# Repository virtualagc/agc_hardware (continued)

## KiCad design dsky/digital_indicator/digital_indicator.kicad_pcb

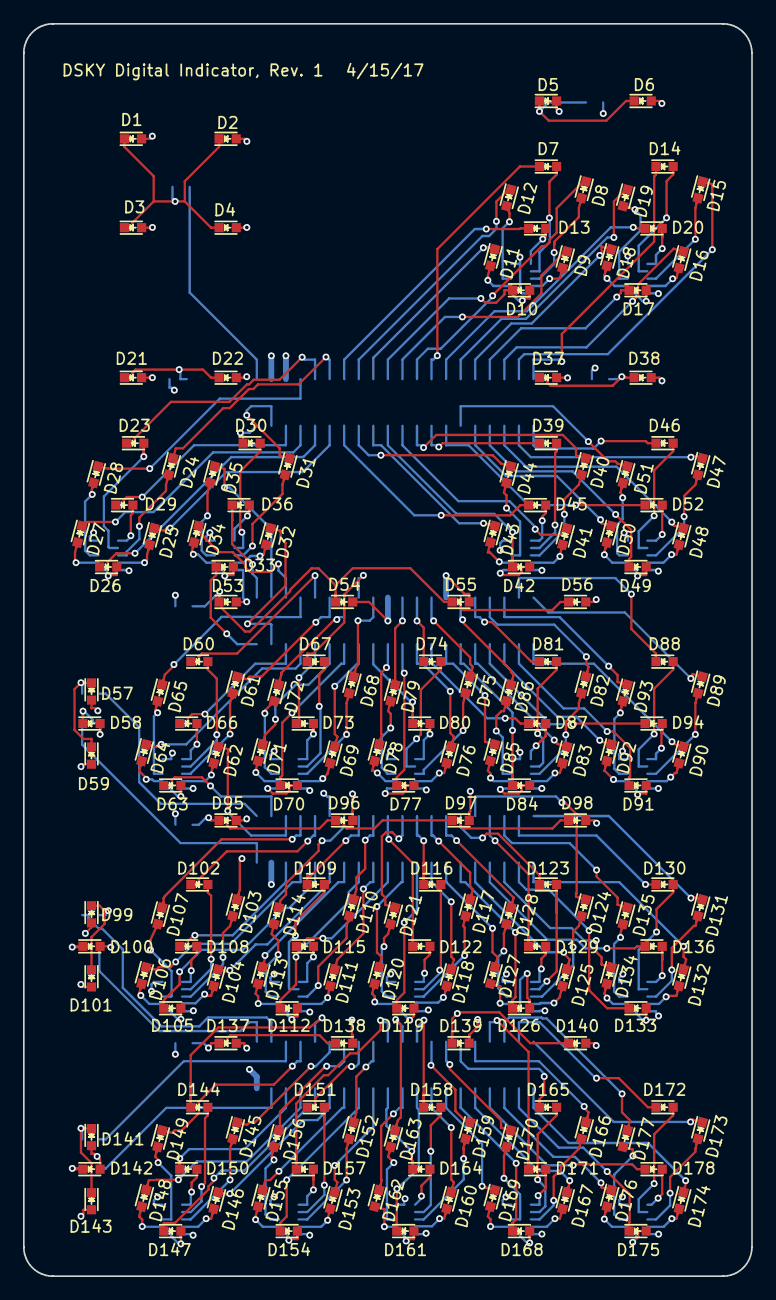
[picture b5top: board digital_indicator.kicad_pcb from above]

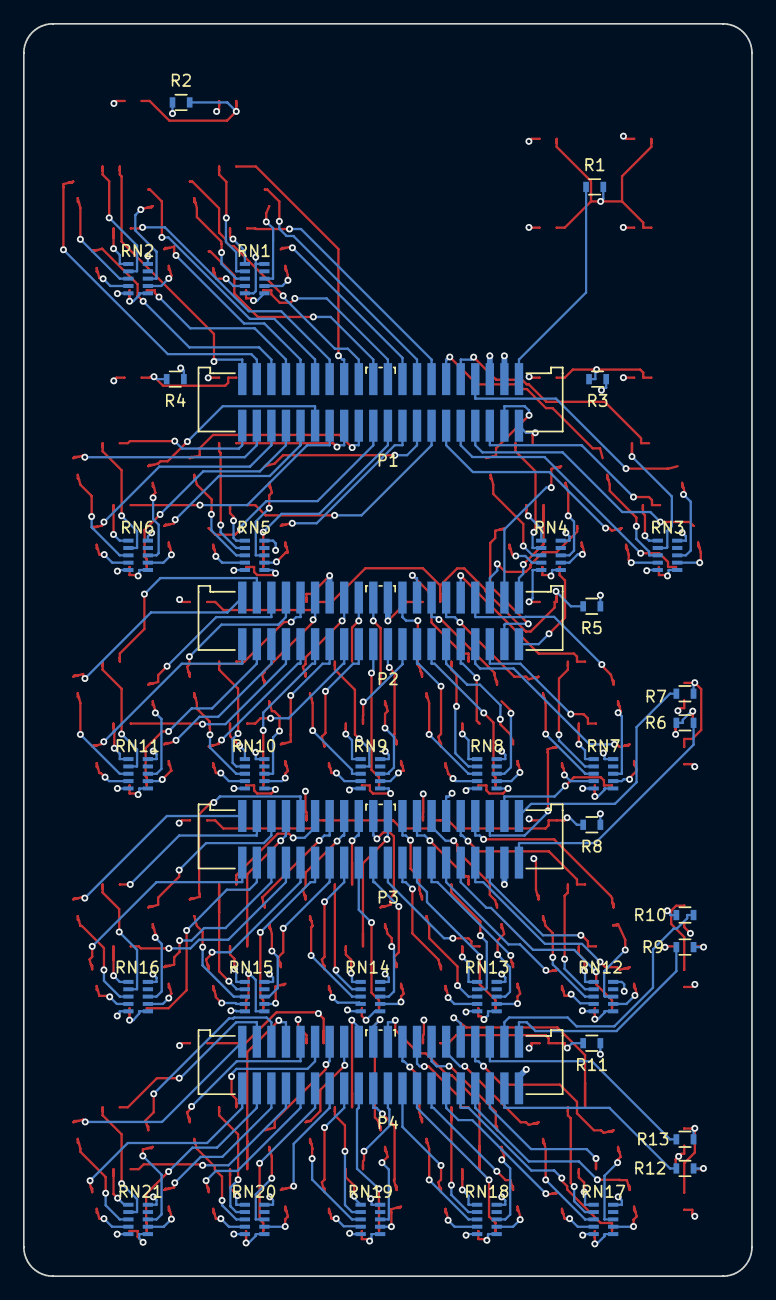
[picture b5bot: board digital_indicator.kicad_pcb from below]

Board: 4 copper layers, 63.5 x 109.2 mm, 217 parts (38 on the bottom side), 316 nets.

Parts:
D1, D2, D3, D4, D5, D6, D7, D8, D9, D10, D11, D12, D13, D14, D15, D16, D17, D18, D19, D20, D21, D22, D23, D24, D25, D26, D27, D28, D29, D30, D31, D32, D33, D34, D35, D36, D37, D38, D39, D40, D41, D42, D43, D44, D45, D46, D47, D48, D49, D50, D51, D52, D53, D54, D55, D56, D57, D58, D59, D60, D61, D62, D63, D64, D65, D66, D67, D68, D69, D70, D71, D72, D73, D74, D75, D76, D77, D78, D79, D80, D81, D82, D83, D84, D85, D86, D87, D88, D89, D90, D91, D92, D93, D94, D95, D96, D97, D98, D99, D100, D101, D102, D103, D104, D105, D106, D107, D108, D109, D110, D111, D112, D113, D114, D115, D116, D117, D118, D119, D120, D121, D122, D123, D124, D125, D126, D127, D128, D129, D130, D131, D132, D133, D134, D135, D136, D137, D138, D139, D140, D141, D142, D143, D144, D145, D146, D147, D148, D149, D150, D151, D152, D153, D154, D155, D156, D157, D158, D159, D160, D161, D162, D163, D164, D165, D166, D167, D168, D169, D170, D171, D172, D173, D174, D175, D176, D177, D178: LED; LED-0603
G1: LOGO; digital_indicator_outlines
P1, P2, P3, P4: CONN_02X20; SHF-120-01-L-D-SM
R1, R5, R8, R11: 250; R_0603
R2, R3, R4, R7, R10, R13: 500; R_0603
R6, R9, R12: 1k; R_0603
RN1, RN2, RN3, RN4, RN5, RN6, RN7, RN8, RN9, RN10, RN11, RN12, RN13, RN14, RN15, RN16, RN17, RN18, RN19, RN20, RN21: R8_BUSSED; R8_746

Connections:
+12V: D1.2, D2.2, D3.2, D4.2, D5.2, D6.2, D21.2, D22.2, D37.2, D38.2, D53.2, D54.2, D55.2, D56.2, D57.2, D58.2, D59.2, D95.2, D96.2, D97.2, D98.2, D99.2, D100.2, D101.2, D137.2, D138.2, D139.2, D140.2, D141.2, D142.2, D143.2, P1.36, P2.14, P2.22, P3.37, RN1.5, RN1.10, RN2.5, RN2.10, RN3.5, RN3.10, RN4.5, RN4.10, RN5.5, RN5.10, RN6.5, RN6.10, RN7.5, RN7.10, RN8.5, RN8.10, RN9.5, RN9.10, RN10.5, RN10.10, RN11.5, RN11.10, RN12.5, RN12.10, RN13.5, RN13.10, RN14.5, RN14.10, RN15.5, RN15.10, RN16.5, RN16.10, RN17.5, RN17.10, RN18.5, RN18.10, RN19.5, RN19.10, RN20.5, RN20.10, RN21.5, RN21.10
COMACT: P1.40, R1.1
GND: P1.38, P4.39, R2.1, R3.1, R4.1, R5.1, R8.1, R11.1
MD1_A: D7.1, P1.16
MD1_B: D8.1, P1.18
MD1_C: D9.1, P1.20
MD1_D: D10.1, P1.22
MD1_E: D11.1, P1.24
MD1_F: D12.1, P1.26
MD1_G: D13.1, P1.28
MD2_A: D14.1, P1.2
MD2_B: D15.1, P1.4
MD2_C: D16.1, P1.6
MD2_D: D17.1, P1.8
MD2_E: D18.1, P1.10
MD2_F: D19.1, P1.12
MD2_G: D20.1, P1.14
ND1_A: D39.1, P1.15
ND1_B: D40.1, P1.17
ND1_C: D41.1, P1.19
ND1_D: D42.1, P1.21
ND1_E: D43.1, P1.23
ND1_F: D44.1, P1.25
ND1_G: D45.1, P1.27
ND2_A: D46.1, P1.1
ND2_B: D47.1, P1.3
ND2_C: D48.1, P1.5
ND2_D: D49.1, P1.7
ND2_E: D50.1, P1.9
ND2_F: D51.1, P1.11
ND2_G: D52.1, P1.13
unnamed: D1.1, D2.1, D3.1, D4.1, R1.2
unnamed: D5.1, D6.1, R2.2
unnamed: D7.2, RN1.2
unnamed: D8.2, RN1.3
unnamed: D9.2, RN1.4
unnamed: D10.2, RN1.6
unnamed: D11.2, RN1.7
unnamed: D12.2, RN1.8
unnamed: D13.2, RN1.1
unnamed: D14.2, RN2.2
unnamed: D15.2, RN2.3
unnamed: D16.2, RN2.4
unnamed: D17.2, RN2.6
unnamed: D18.2, RN2.7
unnamed: D19.2, RN2.8
unnamed: D20.2, RN2.1
unnamed: D21.1, D22.1, R3.2
unnamed: D23.2, RN3.2
unnamed: D24.2, RN3.3
unnamed: D25.2, RN3.4
unnamed: D26.2, RN3.6
unnamed: D27.2, RN3.7
unnamed: D28.2, RN3.8
unnamed: D29.2, RN3.1
unnamed: D30.2, RN4.2
unnamed: D31.2, RN4.3
unnamed: D32.2, RN4.4
unnamed: D33.2, RN4.6
unnamed: D34.2, RN4.7
unnamed: D35.2, RN4.8
unnamed: D36.2, RN4.1
unnamed: D37.1, D38.1, R4.2
unnamed: D39.2, RN5.2
unnamed: D40.2, RN5.3
unnamed: D41.2, RN5.4
unnamed: D42.2, RN5.6
unnamed: D43.2, RN5.7
unnamed: D44.2, RN5.8
unnamed: D45.2, RN5.1
unnamed: D46.2, RN6.2
unnamed: D47.2, RN6.3
unnamed: D48.2, RN6.4
unnamed: D49.2, RN6.6
unnamed: D50.2, RN6.7
unnamed: D51.2, RN6.8
unnamed: D52.2, RN6.1
unnamed: D53.1, D54.1, D55.1, D56.1, R5.2
unnamed: D57.1, D59.1, R7.1
unnamed: D58.1, R6.1
unnamed: D60.2, RN7.2
unnamed: D61.2, RN7.3
unnamed: D62.2, RN7.4
unnamed: D63.2, RN7.6
unnamed: D64.2, RN7.7
unnamed: D65.2, RN7.8
unnamed: D66.2, RN7.1
unnamed: D67.2, RN8.2
unnamed: D68.2, RN8.3
unnamed: D69.2, RN8.4
unnamed: D70.2, RN8.6
unnamed: D71.2, RN8.7
unnamed: D72.2, RN8.8
unnamed: D73.2, RN8.1
unnamed: D74.2, RN9.2
unnamed: D75.2, RN9.3
unnamed: D76.2, RN9.4
unnamed: D77.2, RN9.6
unnamed: D78.2, RN9.7
unnamed: D79.2, RN9.8
unnamed: D80.2, RN9.1
unnamed: D81.2, RN10.2
unnamed: D82.2, RN10.3
unnamed: D83.2, RN10.4
unnamed: D84.2, RN10.6
unnamed: D85.2, RN10.7
unnamed: D86.2, RN10.8
unnamed: D87.2, RN10.1
unnamed: D88.2, RN11.2
unnamed: D89.2, RN11.3
unnamed: D90.2, RN11.4
unnamed: D91.2, RN11.6
unnamed: D92.2, RN11.7
unnamed: D93.2, RN11.8
unnamed: D94.2, RN11.1
unnamed: D95.1, D96.1, D97.1, D98.1, R8.2
unnamed: D100.1, R9.1
unnamed: D99.1, D101.1, R10.1
unnamed: D102.2, RN12.2
unnamed: D103.2, RN12.3
unnamed: D104.2, RN12.4
unnamed: D105.2, RN12.6
unnamed: D106.2, RN12.7
unnamed: D107.2, RN12.8
unnamed: D108.2, RN12.1
unnamed: D109.2, RN13.2
unnamed: D110.2, RN13.3
unnamed: D111.2, RN13.4
unnamed: D112.2, RN13.6
unnamed: D113.2, RN13.7
unnamed: D114.2, RN13.8
unnamed: D115.2, RN13.1
unnamed: D116.2, RN14.2
unnamed: D117.2, RN14.3
unnamed: D118.2, RN14.4
unnamed: D119.2, RN14.6
unnamed: D120.2, RN14.7
unnamed: D121.2, RN14.8
unnamed: D122.2, RN14.1
unnamed: D123.2, RN15.2
unnamed: D124.2, RN15.3
unnamed: D125.2, RN15.4
unnamed: D126.2, RN15.6
unnamed: D127.2, RN15.7
unnamed: D128.2, RN15.8
unnamed: D129.2, RN15.1
unnamed: D130.2, RN16.2
unnamed: D131.2, RN16.3
unnamed: D132.2, RN16.4
unnamed: D133.2, RN16.6
unnamed: D134.2, RN16.7
unnamed: D135.2, RN16.8
unnamed: D136.2, RN16.1
unnamed: D137.1, D138.1, D139.1, D140.1, R11.2
unnamed: D141.1, D143.1, R13.1
unnamed: D142.1, R12.1
unnamed: D144.2, RN17.2
unnamed: D145.2, RN17.3
unnamed: D146.2, RN17.4
unnamed: D147.2, RN17.6
unnamed: D148.2, RN17.7
unnamed: D149.2, RN17.8
unnamed: D150.2, RN17.1
unnamed: D151.2, RN18.2
unnamed: D152.2, RN18.3
unnamed: D153.2, RN18.4
unnamed: D154.2, RN18.6
unnamed: D155.2, RN18.7
unnamed: D156.2, RN18.8
unnamed: D157.2, RN18.1
unnamed: D158.2, RN19.2
unnamed: D159.2, RN19.3
unnamed: D160.2, RN19.4
unnamed: D161.2, RN19.6
unnamed: D162.2, RN19.7
unnamed: D163.2, RN19.8
unnamed: D164.2, RN19.1
unnamed: D165.2, RN20.2
unnamed: D166.2, RN20.3
unnamed: D167.2, RN20.4
unnamed: D168.2, RN20.6
unnamed: D169.2, RN20.7
unnamed: D170.2, RN20.8
unnamed: D171.2, RN20.1
unnamed: D172.2, RN21.2
unnamed: D173.2, RN21.3
unnamed: D174.2, RN21.4
unnamed: D175.2, RN21.6
unnamed: D176.2, RN21.7
unnamed: D177.2, RN21.8
unnamed: D178.2, RN21.1
R1+: P3.40, R7.2
R1-: P3.39, R6.2
R1D1_A: D60.1, P2.32
R1D1_B: D61.1, P2.30
R1D1_C: D62.1, P3.36
R1D1_D: D63.1, P3.38
R1D1_E: D64.1, P2.33
R1D1_F: D65.1, P2.34
R1D1_G: D66.1, P2.35
R1D2_A: D67.1, P2.26
R1D2_B: D68.1, P2.24
R1D2_C: D69.1, P2.25
R1D2_D: D70.1, P2.27
R1D2_E: D71.1, P2.29
R1D2_F: D72.1, P2.28
R1D2_G: D73.1, P2.31
R1D3_A: D74.1, P2.18
R1D3_B: D75.1, P2.16
R1D3_C: D76.1, P2.17
R1D3_D: D77.1, P2.19
R1D3_E: D78.1, P2.21
R1D3_F: D79.1, P2.20
R1D3_G: D80.1, P2.23
R1D4_A: D81.1, P2.10
R1D4_B: D82.1, P2.8
R1D4_C: D83.1, P2.9
R1D4_D: D84.1, P2.11
R1D4_E: D85.1, P2.13
R1D4_F: D86.1, P2.12
R1D4_G: D87.1, P2.15
R1D5_A: D88.1, P2.4
R1D5_B: D89.1, P2.2
R1D5_C: D90.1, P2.1
R1D5_D: D91.1, P2.3
R1D5_E: D92.1, P2.5
R1D5_F: D93.1, P2.6
R1D5_G: D94.1, P2.7
R2+: P4.38, R10.2
R2-: P4.40, R9.2
R2D1_A: D102.1, P3.32
R2D1_B: D103.1, P3.30
R2D1_C: D104.1, P3.29
R2D1_D: D105.1, P3.31
R2D1_E: D106.1, P3.33
R2D1_F: D107.1, P3.34
R2D1_G: D108.1, P3.35
R2D2_A: D109.1, P3.26
R2D2_B: D110.1, P3.24
R2D2_C: D111.1, P3.23
R2D2_D: D112.1, P3.25
R2D2_E: D113.1, P3.27
R2D2_F: D114.1, P3.28
R2D2_G: D115.1, P3.21
R2D3_A: D116.1, P3.18
R2D3_B: D117.1, P3.16
R2D3_C: D118.1, P3.15
R2D3_D: D119.1, P3.17
R2D3_E: D120.1, P3.19
R2D3_F: D121.1, P3.20
R2D3_G: D122.1, P3.22
R2D4_A: D123.1, P3.12
R2D4_B: D124.1, P3.10
R2D4_C: D125.1, P3.9
R2D4_D: D126.1, P3.11
R2D4_E: D127.1, P3.13
R2D4_F: D128.1, P3.14
R2D4_G: D129.1, P3.8
R2D5_A: D130.1, P3.4
R2D5_B: D131.1, P3.2
R2D5_C: D132.1, P3.1
R2D5_D: D133.1, P3.3
R2D5_E: D134.1, P3.5
R2D5_F: D135.1, P3.6
R2D5_G: D136.1, P3.7
R3+: P4.36, R13.2
R3-: P4.37, R12.2
R3D1_A: D144.1, P4.32
R3D1_B: D145.1, P4.30
R3D1_C: D146.1, P4.29
R3D1_D: D147.1, P4.31
R3D1_E: D148.1, P4.33
R3D1_F: D149.1, P4.34
R3D1_G: D150.1, P4.35
R3D2_A: D151.1, P4.26
R3D2_B: D152.1, P4.24
R3D2_C: D153.1, P4.23
R3D2_D: D154.1, P4.25
R3D2_E: D155.1, P4.27
R3D2_F: D156.1, P4.28
R3D2_G: D157.1, P4.22
R3D3_A: D158.1, P4.18
R3D3_B: D159.1, P4.16
R3D3_C: D160.1, P4.15
R3D3_D: D161.1, P4.17
R3D3_E: D162.1, P4.19
R3D3_F: D163.1, P4.20
R3D3_G: D164.1, P4.21
R3D4_A: D165.1, P4.12
R3D4_B: D166.1, P4.10
R3D4_C: D167.1, P4.9
R3D4_D: D168.1, P4.11
R3D4_E: D169.1, P4.13
R3D4_F: D170.1, P4.14
R3D4_G: D171.1, P4.8
R3D5_A: D172.1, P4.4
R3D5_B: D173.1, P4.2
R3D5_C: D174.1, P4.1
R3D5_D: D175.1, P4.3
R3D5_E: D176.1, P4.5
R3D5_F: D177.1, P4.6
R3D5_G: D178.1, P4.7
VD1_A: D23.1, P1.32
VD1_B: D24.1, P1.30
VD1_C: D25.1, P1.29
VD1_D: D26.1, P1.31
VD1_E: D27.1, P1.33
VD1_F: D28.1, P1.34
VD1_G: D29.1, P1.35
VD2_A: D30.1, P1.39
VD2_B: D31.1, P1.37
VD2_C: D32.1, P2.37
VD2_D: D33.1, P2.39
VD2_E: D34.1, P2.36
VD2_F: D35.1, P2.38
VD2_G: D36.1, P2.40

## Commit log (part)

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2015-10-11 Initial schematicery
2015-10-11 More of page 1 of the timer module (poorly drawn)
2015-10-13 Added PHS3/ from A24-2 since it makes more sense in the timer modules, along with the two monitor signals on A2-1, and an inverter and signal I missed
2015-10-20 Added the start/stop logic to timer page A02-2, and introduced a new part, 74LVC07, that I think will be the solution for open drain things
2015-10-24 Added the final page of the timer module. Leaving top-level wiring pretty bare for now until I have a better idea of what's needed outside the module.
2015-10-25 Beginnings of the SQ Register and Decoding module -- mostly SQ read/write/clear logic
2015-10-27 Renamed components in the timer module to fit the new numbering scheme (module_number * 1000 + part number), and updated initial conditions to make simulation happy again after fixes
2015-10-29 Finished off the SQ Register and Decoder module. Next up is the stage and branch registers
2015-10-29 Added the 'stage' bit of the Stage Branch Decoder module, and cleaned up a lot of initial conditions (still probably a lot to be done there)
2015-10-31 Finished off the first page of the Stage Branch Decoding module.
2015-11-20 Added a library part for a 128-pin DIN 41612 connector. It's unclear if 128 pins will be enough for some modules (yikes) but I'm going to try my hardest to make it work.
2015-11-26 Added the first page of the Crosspoint Generator NQI module. Not dealing with I/O until page 2 is also present...
2015-12-19 Finished the second page of crosspoint generator 1 and tied it into the rest of the system.
    Turns out most documentation online is wrong, and block 2 modules have 276 pins per module to the backplane, rather than the 140-144 that is quoted everywhere (those are block 1 figures). Instead of 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
2015-12-22 Page 2 of module 6, plus a few corrections.
    Changed RPTSET in module 3 from an output to an input. Dropped unneeded
    pullups from R1C/ (turns out this missing one is in module 6) and RB1/
    (I don't remember why that was there) in module 4.
2015-12-24 A few crosspoint touchups I missed
2015-12-29 Page 2 of the service gates, including some service logic taken from modules 14 and 24 (page 1 got some updates too)
2015-12-29 Broke out some open drain signals that were only partially onto the backplane... I missed them because inouts are sufficient to satisfy an input criterion, so there's no error if only part of the sig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
2016-01-03 More corrections, TC0, CA0, and STD2 all have the right pulses now
2016-01-03 Added the second instance of the two-bit-columns sheet. Wiring of module 8 next
2016-01-06 Fully added / tied in module 9. Yay for identical logic!
2016-01-06 Added a fully tied in module 10.
2016-01-31 Added in WHOMP, whatever it is
2016-02-11 Bux fixes for things found during FPGA integration.
    * A05 was driving TSGN/ directly instead of with an OD buffer+pullup
    * Some bad logic with crosspoints in module 5
    * A bad part number in module 12
    * Removal of unused signals from the backplane connectors
    * Addition of some monitor signals from the timer to the backplane
2016-02-13 First bit of memory timing and addressing (fixed memory timing)
2016-02-17 Corrected a couple of bugs found by Quartus (L16/, Z15/, Z16/ not connected)
2016-02-21 Added and tied in module 15, the rupt service (and banking/rope+strand selection)
2016-02-28 Updated fixed memory model, plus various bugfixes
    Rope memory control signals are now decoded much earlier in the cycle to
    determine the target address, allowing slower memory devices (such as
    the EPCS on the DE0 Nano) enough time to load their data.
    The bugfixes are mostly wiring errors discovered by debugging lockups in
    when running Colossus 237 -- all were causing the ST2 pulse to not
    occur, so errors that *don't* prevent ST2 from happening very well might
2016-03-06 Higher fidelity rope logic that doesn't break with DV.
    Divide, somewhat strangely, handles the ropes differently during its
    execution than any other instruction (at least, that I've seen). It does
    full cycles on a rope, just without strobing the sense amplifiers at the
    end. Plus, that rope is kinda random -- DV1 timepulse 8 seems to set bit
    12 of S for some reason. Anyways, I had to switch to three edge
    detectors that clear the A/B/C quarter latches with the RESETA, RESETB,
2016-03-06 New bidirectional codegen flags for the MRAM chip.
2016-03-26 Added in counter cell 2.
    I moved some logic from module 5 that's related to counters into page 1,
    and completely moved page 2 out, since it has more to do with monitor
    stuff. That'll show up as page 2 of module 13.
2016-04-01 Added and tied in the Alarms module.
    I've placed page 2 of Counter Cell 2 here as page 2 of alarms. It didn't
    fit in the counter cells, despite producing a few counter-related
    signals -- and it mostly handles monitor stuff, which is a good fit for
    what's going on here. As part of this I modernized the timer and scaler
    connectors.
    There seems to be lots of oscillations in the the simulation. Initial
2016-04-09 Inout IV. Not yet tied into the backplane.
2016-04-09 Tied in Inout IV and renamed MONPCH to the original MON+CH
2016-04-10 Inout II. Not yet tied in.
2016-04-12 Added and tied in Inout I
2016-04-16 Added most of the rest of Inout III and tied it in. Still not sure where to put the downlink stuff, standby, and CHOR propers.
2016-04-17 Added and tied in Inout V.
2016-04-20 Added interrupt inhibition to module 3
2016-04-21 Added and tied in Inout VII, the final logic module!
    I still need to comb through the schematics to see if there are any
    stray gates I missed. The initial conditions are also pretty much
    guaranteed to be wrong. But it's mostly all there!
2016-04-22 Lots of initial conditions, some missed gates, and some wiring fixes
2016-04-28 Did another pass through the schematics and added in some missing gates
2016-04-30 Broke out most (all?) of the DSKY outputs
2016-05-05 Corrected RESTART light polarity in the alarms module
2016-07-23 Added some missing net names.
2016-07-24 Broke out some PIPA and CDU-related output signals, and fixed the polarity of PIPPLS/
2016-09-10 Add a basic README
2016-09-18 Corrected a wiring error in the Monitor request logic (ST1 in place of ST0) and an initial condition problem in the scaler causing the computer to come up with night watchman alarm
2016-10-04 Some initial condition updates to fix a couple oscillating signals I found
2016-10-05 Fixed memory: inhibit reads if no rope is selected, which can happen when addressing non-present memory
2016-10-08 Not gate rewiring up through module 11, with other cleanup here and there
2016-10-15 Removed some unused aliases from the part library
2016-10-23 Added switched and unswitched power nets to the Timer. Also fixed a few glitches in the new library parts.
2016-10-23 Switched SQ Register & Decoder over to +4VSW and fixed some straggling VCCs in Timer
2016-10-23 Updated Crosspoint NQI to be on +4VSW
2016-10-24 Updated Service Gates to be on +4VSW
2016-10-24 Updated Four Bit 2 to be on +4VSW. Performed the same consolidation as in 1.
2016-10-26 Updated Four Bit 3 to be on +4VSW. Performed the same consolidation as in 1+2.
2016-10-26 Updated Parity and S Register to be on +4VSW
2016-10-31 Updated Memory Timing and Addressing to be on +4VSW
2016-11-01 Updated Inout I to be on +4VSW
2016-11-01 Updated Inout II to be on +4VSW
2016-11-01 Updated Inout IV to be on +4VSW
2016-11-02 Updated Inout VI to be on +4VSW
2016-11-02 Fixed/erasable memory on switched power, and voltage pin updates for the memories and tristate buffers
2016-11-02 Pulled TIMR generation off of standby power, and consolidated some parts
2016-11-02 Some designator fixes for four bit 4, which apparently halfway thought it was module 10
2016-11-05 New (original) seven-segment decoder, taken from the Apollo 12 Mission Report
2016-11-06 Added in the rest of the IDM hardware. Values and diode matrix design still need to be finalized. Working on wiring everything up now.
2016-11-06 Finished initial wiring of the Indicator Driver Module. Currently sitting at 111 pins used, so I've been too aggressive at culling pins
2016-11-06 Added a preliminary digital indicator board. Currently planning on custom 7SDs.
2016-11-06 Added a DSKY keyboard board, which should be it for the DSKY outside of the backplane. Currently assuming I'll be making my own keys
2016-11-07 The AGC only generates KEYRUPTs when it gets a non-zero keycode, so PRO can safely be on the keyboard reset chain.
2016-11-07 The LM System Handbook, however, shows that PRO is *not* on the reset chain...
    Revert "The AGC only generates KEYRUPTs when it gets a non-zero keycode, so PRO can safely be on the keyboard reset chain."
    This reverts commit 773c8305ed61eff056e970f90c0f0f145b3fc18d.
2016-11-23 Fixed a label that became disconnected in module 6, causing DV to sometimes go off the rails
2017-03-25 Removed the '1' initial condition from the GOJ1 gate
2017-04-08 Preliminary LED layout for digital indicator board, plus connector and resistor network footprints
2017-04-17 Rev. 1 of the Digital Indicator board
2017-05-15 Broke out the signals needed for downlink
2017-05-20 Updated the README
2017-05-22 Added a footprint for the EC2-12TNU relay
2017-05-22 Added PCN10A-128P and EC2-12NU footprints
2017-06-09 Changed STRT2 to MYCLMP in module A14, per ND-1021042. Apparently there are *two* signals named STRT2 in the AGC, and the schematics don't differentiate them.
2017-06-26 Digitized the Relay Matrix schematic diagram from ND-1021042 for the DSKY backplane
2017-11-18 Preliminary work on a new design using 74HC05 for all gates.
2018-03-13 Added a simple 9x16 0.125"-pitch board for making an AGC test connector cable
2018-03-13 Imported all (I think) Tray A nets into Delphi
2018-03-17 Delphi: Import pins for modules A8-A11
2018-03-18 Delphi: Import pins for modules A25-A31
2018-03-18 Delphi: corrected a handful of pin errors. More to come.
2018-03-26 Delphi: A number of pin corrections
2018-03-26 Delphi: More corrections. All OUTs have associated INs (except for CO02, which really didn't have a destination)
2018-04-30 Delphi: fixed pins in A30/A31, created an index for nets in the pin table, and other minor fixes
2018-05-13 Delphi: Updated some pins
2018-05-18 Delphi: imported pins for B1-B6
2018-05-18 Delphi: imported pins for B11-B17
2018-05-21 Delphi: added in a missing pin on A30-A31 and marked a couple of guesses
2018-05-23 Delphi: imported pins for B61, B62, B63, B41, and B42
2018-05-25 Delphi: Removed MYCLMP references
2018-06-05 Delphi: Corrected remaining Tray B errors, as currently defined
2018-06-22 Added schematics for B9/B10
2018-06-25 Added a preliminary schematic for B11. It is 100% definitely incorrect/incomplete, but hopefully should be able to more fully reconstructed soon.
2018-07-04 Initial work on B13-B14
2018-07-06 Delphi: almost completed A51, resolved most remaining unknowns on A modules, and started in on A61-A63
2018-07-06 Delphi: Some I/O type corrections for newly placed pins
2018-07-07 Fully pinned out A61-A63 (except for BPLUS/BPLSSW and +4VDC/+4SW ambiguity)
2018-07-07 Delphi: updated B61-B63 to match the pinned out A61-A63. Aside from the mystery thermistor, and power ambiguity, they are fully pinned out.
2018-07-08 Delphi: completed pinning out B41 and B42
2018-07-18 Delphi: updated power supply unknowns per findings on AGC 602
2018-07-19 Delpih: changed all of the D28SHT pins to BP, since neither 2003100- nor 2003993- series power supplies had anything on those pins
2018-08-11 Delphi: Corrected through B17 using the AGC Handbook. Configuration now matches 2003993 AGCs as close as we currently know
2018-09-22 Delphi: Marked floating inputs in the notes field, rather than NC+0VDCA.
2018-09-23 Delphi: added some descriptions for some R-type output circuits (all that are used in the LM).
2018-10-09 Delphi: Added pin table for 2003100-071 wiring configuration
2018-10-29 This adds fixes to the schematics for changes identified in comparing against the independent AGC schematics in the "schematics" branch of the main Virtual AGC repository. Changes include: Topologica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
